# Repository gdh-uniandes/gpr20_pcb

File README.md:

# GPR20: PCB
Repository for the printed circuit board (PCB) of the GPR-20 robot. This repository contains the design and manufacture files for the GPR-20 PCB.

## Repository Organization
The repository is organized as follows:
- **GERBER (./gerber/):** contains the manufacture files for the robot PCB as indicated by the Universidad de Los Andes PCB manufacturing laboratory.
- **PROJETC (./project/):** contains [KiCAD](https://www.kicad.org/) project files of the robot PCB.

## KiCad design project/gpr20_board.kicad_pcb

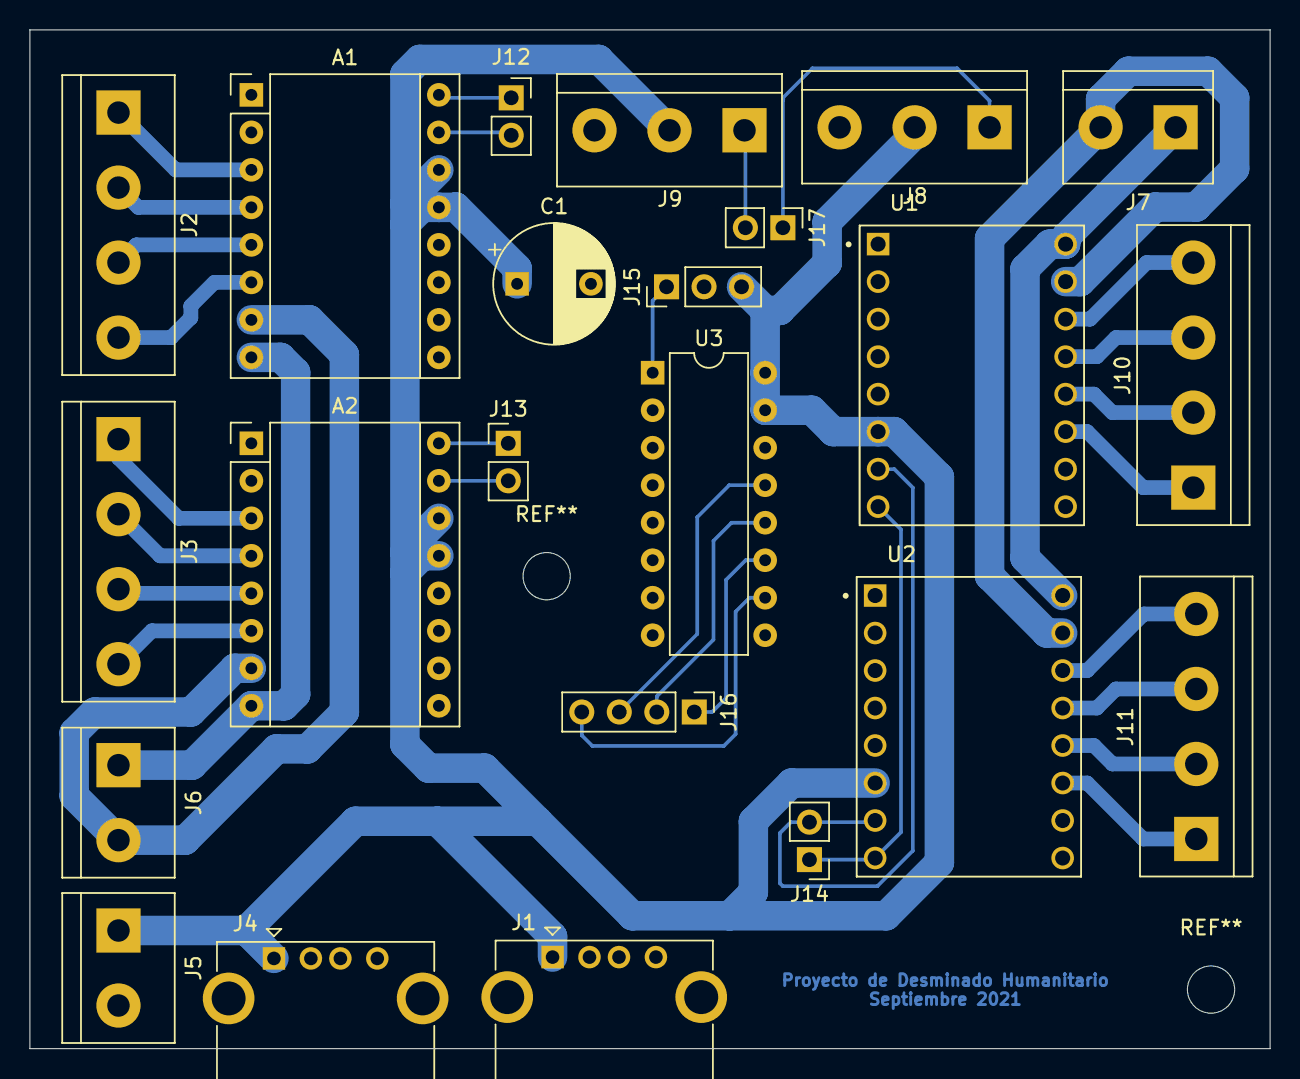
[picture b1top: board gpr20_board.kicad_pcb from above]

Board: 2 copper layers, 84.0 x 69.0 mm, 23 parts (0 on the bottom side), 35 nets.

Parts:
A1, A2: Pololu_Breakout_DRV8825; Pololu_Breakout-16_15.2x20.3mm
C1: 1000uF; CP_Radial_D8.0mm_P5.00mm
J1: USB_RPI; USB_A_CONNFLY_DS1095-WNR0
J2: X_AXIS_MOTOR; TerminalBlock_bornier-4_P5.08mm
J3: Y_AXIS_MOTOR; TerminalBlock_bornier-4_P5.08mm
J4: USB_SCREEN; USB_A_CONNFLY_DS1095-WNR0
J5: 5V_IN; TerminalBlock_bornier-2_P5.08mm
J6: 9V_IN; TerminalBlock_bornier-2_P5.08mm
J7: 3V3_IN; TerminalBlock_bornier-2_P5.08mm
J8: SEN_EJE_X; TerminalBlock_bornier-3_P5.08mm
J9: SEN_EJE_Y; TerminalBlock_bornier-3_P5.08mm
J10: ANTENNA_MOTOR_0; TerminalBlock_bornier-4_P5.08mm
J11: ANTENNA_MOTOR_1; TerminalBlock_bornier-4_P5.08mm
J12: Conn_01x02; PinSocket_1x02_P2.54mm_Vertical
J13, J14: Conn_01x02; PinHeader_1x02_P2.54mm_Vertical
J15: SENSOR_CONN; PinHeader_1x03_P2.54mm_Vertical
J16: SPI_SENSOR; PinHeader_1x04_P2.54mm_Vertical
J17: SEN_CONN; PinHeader_1x02_P2.54mm_Vertical
U1, U2: POLOLU-2134; MODULE_POLOLU-2134
U3: MCP3008; DIP-16_W7.62mm

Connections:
3V3+: J7.1, U1.16, U2.16
3V3-: J7.2, U1.15, U2.15
5V: A1.13, A1.14, A2.13, A2.14, C1.1, J1.1, J4.1, J5.1, J8.2, J9.2, J15.3, U1.6, U2.6, U3.15, U3.16
9V+: A1.8, A2.8, J6.1
9V-: A1.7, A2.7, J6.2
BOARD07: J8.1, J17.1
BOARD11: J9.1, J17.2
BOARD13: A1.16, J12.1
BOARD15: A1.15, J12.2
BOARD16: A2.16, J13.1
BOARD18: A2.15, J13.2
BOARD19: J16.1, U3.11
BOARD21: J16.2, U3.12
BOARD23: J16.3, U3.13
BOARD24: J16.4, U3.10
BOARD38: J14.1, U1.8, U2.8
BOARD40: J14.2, U1.7, U2.7
GND: A1.1, A1.10, A1.11, A1.12, A2.1, A2.10, A2.11, A2.12, C1.2, J1.4, J1.5, J4.4, J4.5, J5.2, J8.3, J9.3, J15.2, U1.2, U1.3, U1.9, U2.2, U2.3, U2.9, U3.9, U3.14
unnamed: A1.3, J2.1
unnamed: A1.4, J2.2
unnamed: A1.5, J2.3
unnamed: A1.6, J2.4
unnamed: A2.3, J3.1
unnamed: A2.4, J3.2
unnamed: A2.5, J3.3
unnamed: A2.6, J3.4
unnamed: J10.1, U1.11
unnamed: J10.2, U1.12
unnamed: J10.3, U1.13
unnamed: J10.4, U1.14
unnamed: J11.1, U2.11
unnamed: J11.2, U2.12
unnamed: J11.3, U2.13
unnamed: J11.4, U2.14
unnamed: J15.1, U3.1

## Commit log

2022-02-25 Project files for GPR-20 PCB
2022-02-25 Manufacture files for GPR-20 PCB
2022-02-25 README file for GPR-20 PCB repository
